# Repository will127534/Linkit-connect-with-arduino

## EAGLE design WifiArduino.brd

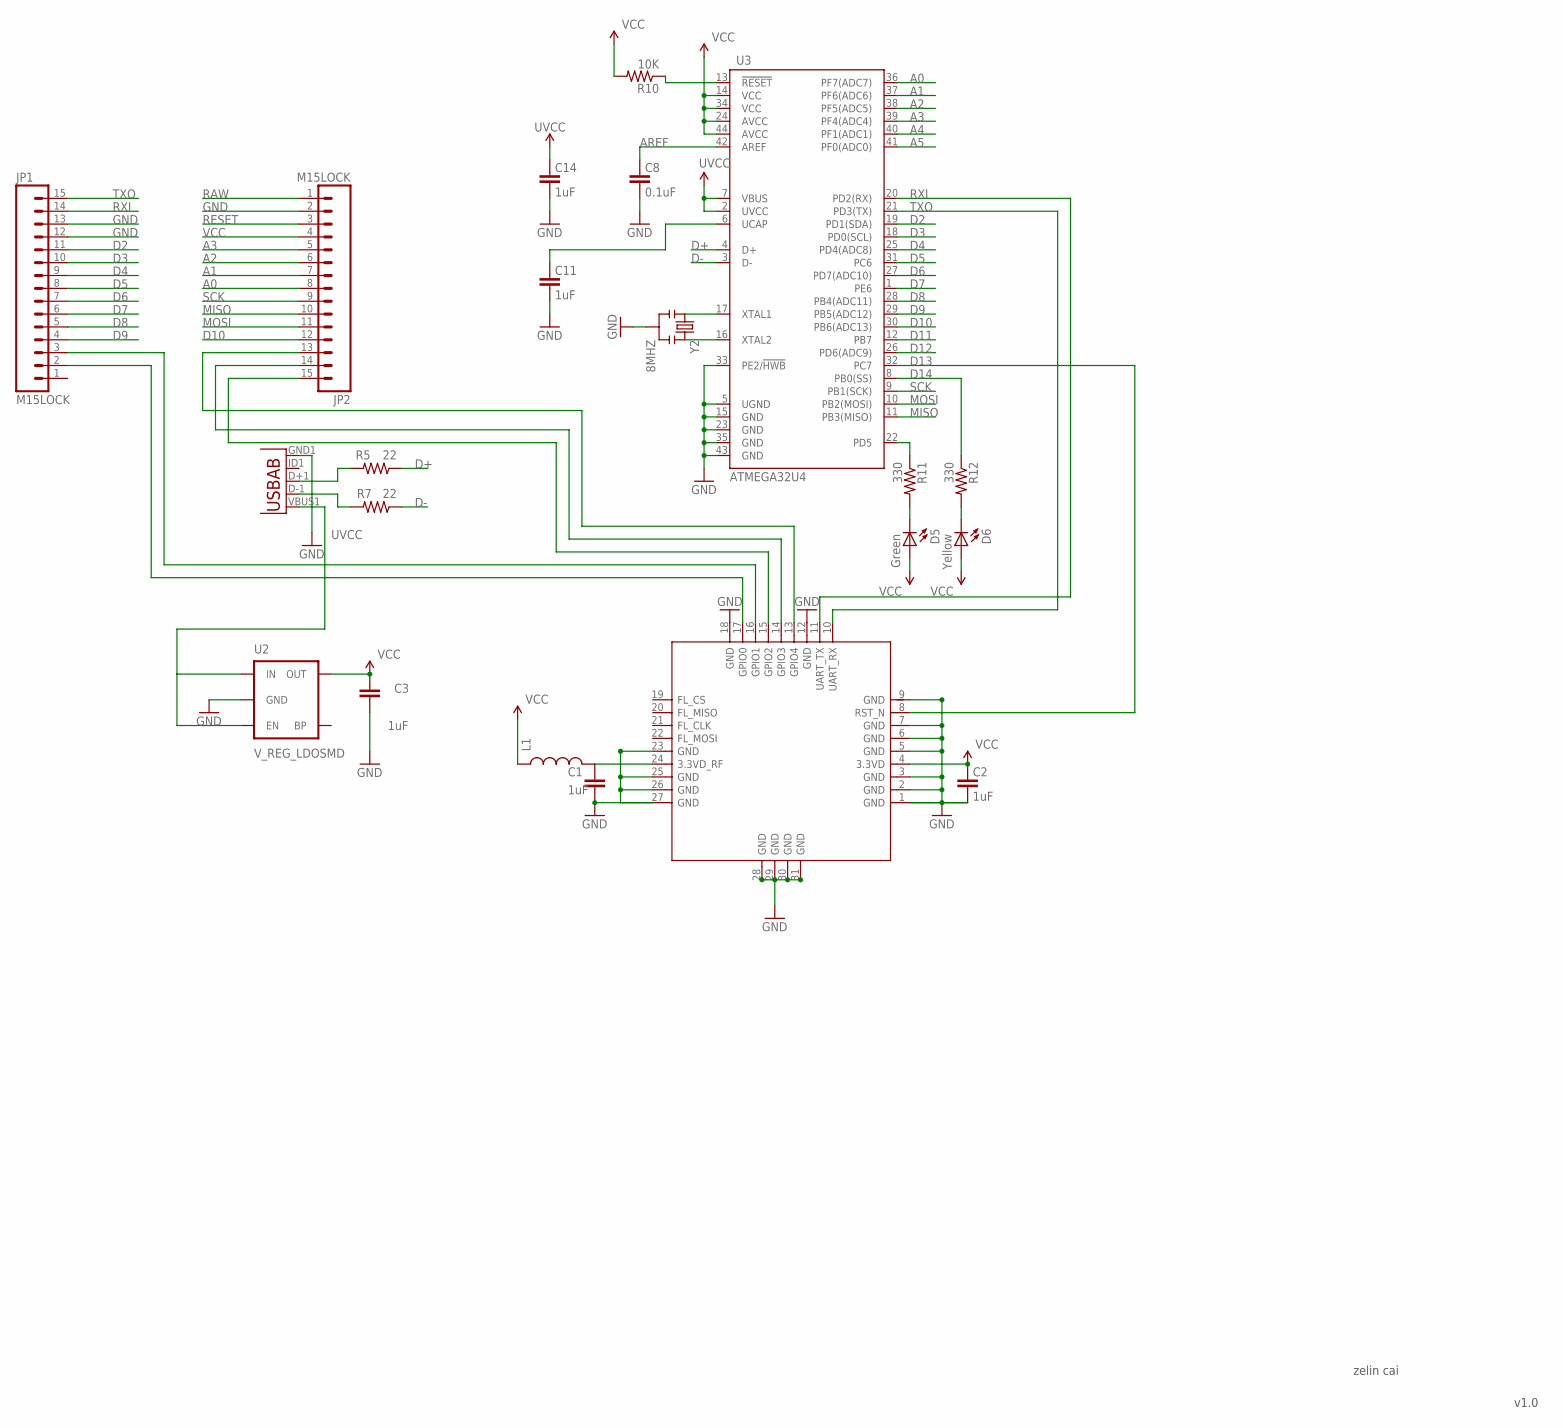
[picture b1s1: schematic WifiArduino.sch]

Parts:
C1, C2, C3: 1uF; 0805
C8: 0.1uF; 0603-CAP
C11, C14: 1uF; 0603-CAP
D5: Green; LED-0603
D6: Yellow; LED-0603
JP1, JP2: M15LOCK; 1X15_LOCK
L1: INDUCTOR0805; 0805
R5, R7: 22; 0603-RES
R10: 10K; 0603-RES
R11, R12: 330; 0603-RES
U1: MT7681_MOD; 31P-L18.0XW15.0MM
U2: V_REG_LDOSMD; SOT23-5
U3: ATMEGA32U4; QFN-44-NOPAD_1:1-OUTFAKES
X1: USB-ABIN&OUT; USB-AB-MICRO-SMD-V03-IN&OUT
Y2: 8MHZ; RESONATOR-SMD

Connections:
3.3V: C2.2, C3.2, D5.A, D6.A, L1.1, R10.2, U1.4 (3.3VD), U2.5 (OUT)
A0: JP2.8, U3.36 (PF7(ADC7))
A1: JP2.7, U3.37 (PF6(ADC6))
A2: JP2.6, U3.38 (PF5(ADC5))
A3: JP2.5, U3.39 (PF4(ADC4))
A4: U3.40 (PF1(ADC1))
A5: U3.41 (PF0(ADC0))
AREF: C8.2, U3.42 (AREF)
D2: JP1.11, U3.19 (PD1(SDA))
D3: JP1.10, U3.18 (PD0(SCL))
D4: JP1.9, U3.25 (PD4(ADC8))
D5: JP1.8, U3.31 (PC6)
D6: JP1.7, U3.27 (PD7(ADC10))
D7: JP1.6, U3.1 (PE6)
D8: JP1.5, U3.28 (PB4(ADC11))
D9: JP1.4, U3.29 (PB5(ADC12))
D10: JP2.12, U3.30 (PB6(ADC13))
D11: U3.12 (PB7)
D12: U3.26 (PD6(ADC9))
D13: U1.8 (RST_N), U3.32 (PC7)
D14: R12.1, U3.8 (PB0(SS))
D+: R5.1, U3.4 (D+)
D-: R7.1, U3.3 (D-)
GND: C1.1, C2.1, C3.1, C8.1, C11.1, C14.1, JP1.12, JP1.13, JP2.2, U1.1 (GND), U1.2 (GND), U1.3 (GND), U1.5 (GND), U1.6 (GND), U1.7 (GND), U1.9 (GND), U1.12 (GND), U1.18 (GND), U1.23 (GND), U1.25 (GND), U1.26 (GND), U1.27 (GND), U1.28 (GND), U1.29 (GND), U1.30 (GND), U1.31 (GND), U2.2 (GND), U3.5 (UGND), U3.15 (GND), U3.23 (GND), U3.33 (PE2/!HWB), U3.35 (GND), U3.43 (GND), X1.GND1 (GND), Y2.2
MISO: JP2.10, U3.11 (PB3(MISO))
MOSI: JP2.11, U3.10 (PB2(MOSI))
unnamed: U3.16 (XTAL2), Y2.3
unnamed: U3.17 (XTAL1), Y2.1
unnamed: C1.2, L1.2, U1.24 (3.3VD_RF)
unnamed: JP2.13, U1.13 (GPIO4)
unnamed: JP2.14, U1.14 (GPIO3)
unnamed: R7.2, X1.D-1 (D-)
unnamed: JP2.15, U1.15 (GPIO2)
unnamed: R5.2, X1.D+1 (D+)
unnamed: JP1.3, U1.16 (GPIO1)
unnamed: JP1.2, U1.17 (GPIO0)
unnamed: R10.1, U3.13 (!RESET)
unnamed: C11.2, U3.6 (UCAP)
unnamed: D6.C, R12.2
unnamed: D5.C, R11.2
RAW: JP2.1
RESET: JP2.3
RXI: JP1.14, U1.11 (UART_TX), U3.20 (PD2(RX))
SCK: JP2.9, U3.9 (PB1(SCK))
TXLED: R11.1, U3.22 (PD5)
TXO: JP1.15, U1.10 (UART_RX), U3.21 (PD3(TX))
UVCC: C14.2, U2.1 (IN), U2.3 (EN), U3.2 (UVCC), U3.7 (VBUS), X1.VBUS1 (VBUS)
VCC: JP2.4, U3.14 (VCC), U3.24 (AVCC), U3.34 (VCC), U3.44 (AVCC)

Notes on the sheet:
zelin cai
v1.0

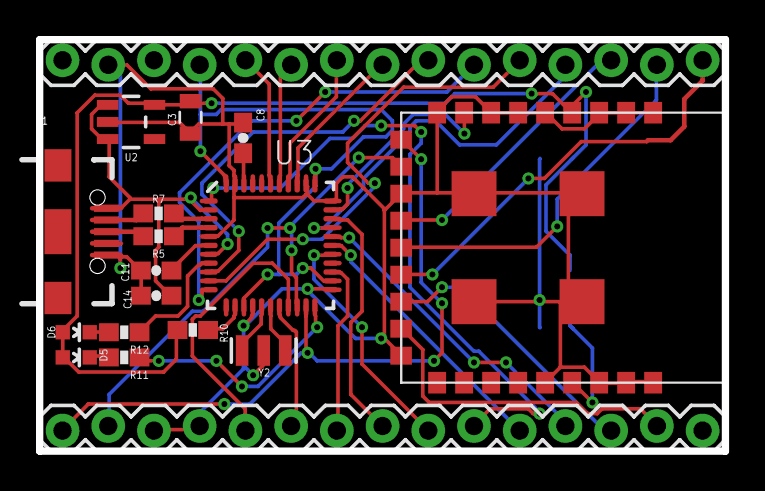
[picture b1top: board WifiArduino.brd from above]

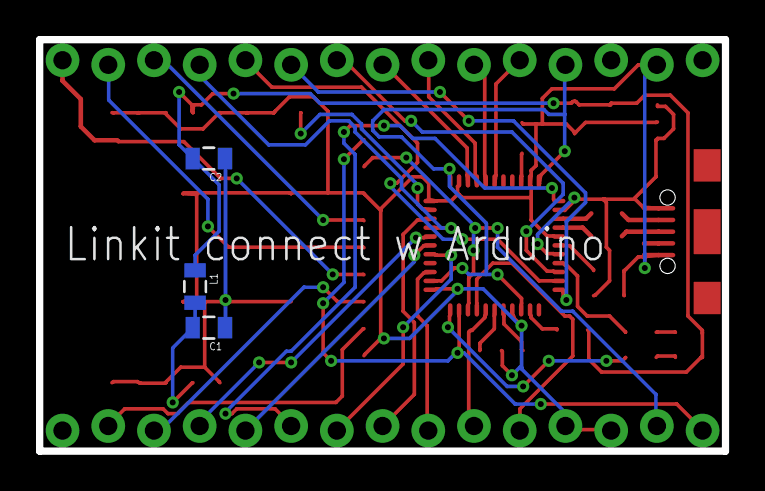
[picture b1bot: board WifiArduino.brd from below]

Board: 2 copper layers, 38.1 x 22.9 mm, 21 parts (3 on the bottom side), 42 nets.

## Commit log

2015-03-05 :neckbeard: Added .gitattributes & .gitignore files
2015-07-04 Upload PCB files

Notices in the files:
parts and their libraries:
SparkFun-FreqCtrl: Licensing: CC v3.0 Share-Alike You are welcome to use this library for commercial purposes.
